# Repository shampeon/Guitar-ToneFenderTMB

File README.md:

A small PCB for the Fender AB763 treble, mid, and bass tone stack. Inspired by Tristan Collins's [Bandmaster PCB](https://github.com/tristancollins/Guitar-ToneBandmaster), with the same dimensions and for the PCB and mounting holes, and created in KiCad 9.

# Components and their values

* R1: 100k (tone slope resistor, 0.5W or greater)
* C1: 250pF (treble capacitor, 400V or greater)
* C2: 100nF/0.1uF (bass capacitor, 400V or greater)
* C3: 4.7nF/0.0047uF (mid capacitor, 400V or greater)
* J1, J2: 2 pin screw terminal, 5mm spacing
* RV1, RV2, RV3: 3 pin screw terminal, 5mm spacing

You can adjust the values of the components to change the behavior of the tone stack. Select the Fender Treble-Mid-Bass tonestack at [Yet Another Tonestack Calculator](https://tonestack.yuriturov.com) to compare the frequency response to the standard values here.

The mid pot in this project is wired as a potentiometer, as in the Bassman 5F6-A, not a variable resistor as in the AB763 black panel amps. This avoids the issue where the signal completely drops out when all the tone pots are turned down.

Rob Robinette has a great [page on how the TMB tone stack works](https://robrobinette.com/How_The_TMB_Tone_Stack_Works.htm).

# Fabricating the PCB

The 53mm x 45mm PCB can be manufactured by any of the online PCB fabrication sites, like [PCBWay](https://pcbway.com) or [JLCPCB](https://jlcpcb.com/). I use PCBWay, so the back text `WayWayWay` will be converted to the PCBWay product number when it is manufactured. You may want to modify this if you use another manufacturer.

A Gerber file ZIP is included in the repository, generated using the PCBWay plugin for KiCad 9.

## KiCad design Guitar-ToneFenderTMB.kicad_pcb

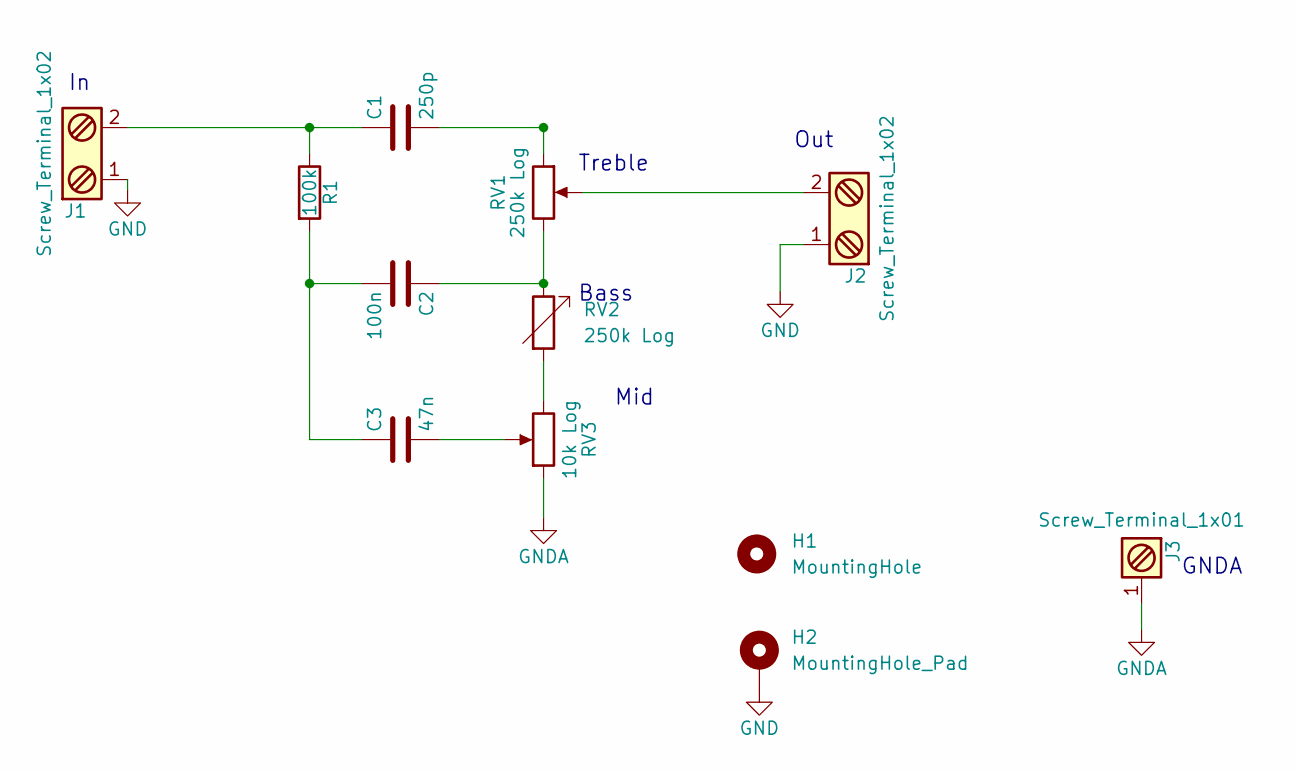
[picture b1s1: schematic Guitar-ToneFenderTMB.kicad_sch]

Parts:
C1: 250p; C_Disc_D7.5mm_W5.0mm_P7.50mm
C2: 100n; C_Rect_L7.2mm_W4.5mm_P5.00mm_FKS2_FKP2_MKS2_MKP2
C3: 47n; C_Axial_L12.0mm_D6.5mm_P15.00mm_Horizontal
H1: MountingHole; MountingHole_3.2mm_M3
H2: MountingHole_Pad; MountingHole_3.2mm_M3_Pad
J1, J2: Screw_Terminal_1x02; PhoenixContact_MCV_1,5_2-G-5.08_1x02_P5.08mm_Vertical
J3: Screw_Terminal_1x01; SolderWire-0.75sqmm_1x01_D1.25mm_OD2.3mm
R1: 100k; R_Axial_DIN0414_L11.9mm_D4.5mm_P15.24mm_Horizontal
RV1: 250k Log; PhoenixContact_MCV_1,5_3-G-5.08_1x03_P5.08mm_Vertical; MPN 1729131
RV2: 250k Log; PhoenixContact_MCV_1,5_3-G-5.08_1x03_P5.08mm_Vertical
RV3: 10k Log; PhoenixContact_MCV_1,5_3-G-5.08_1x03_P5.08mm_Vertical; MPN 1729131

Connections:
GND: H2.1, J1.1, J2.1
GNDA: J3.1, RV3.1
unnamed: C1.1, J1.2, R1.1
unnamed: C1.2, RV1.1
unnamed: C2.1, RV1.3, RV2.1
unnamed: C2.2, C3.1, R1.2
unnamed: C3.2, RV3.2
unnamed: J2.2, RV1.2
unnamed: RV2.2, RV3.3

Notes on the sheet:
Treble
Out
Bass
Mid
GNDA

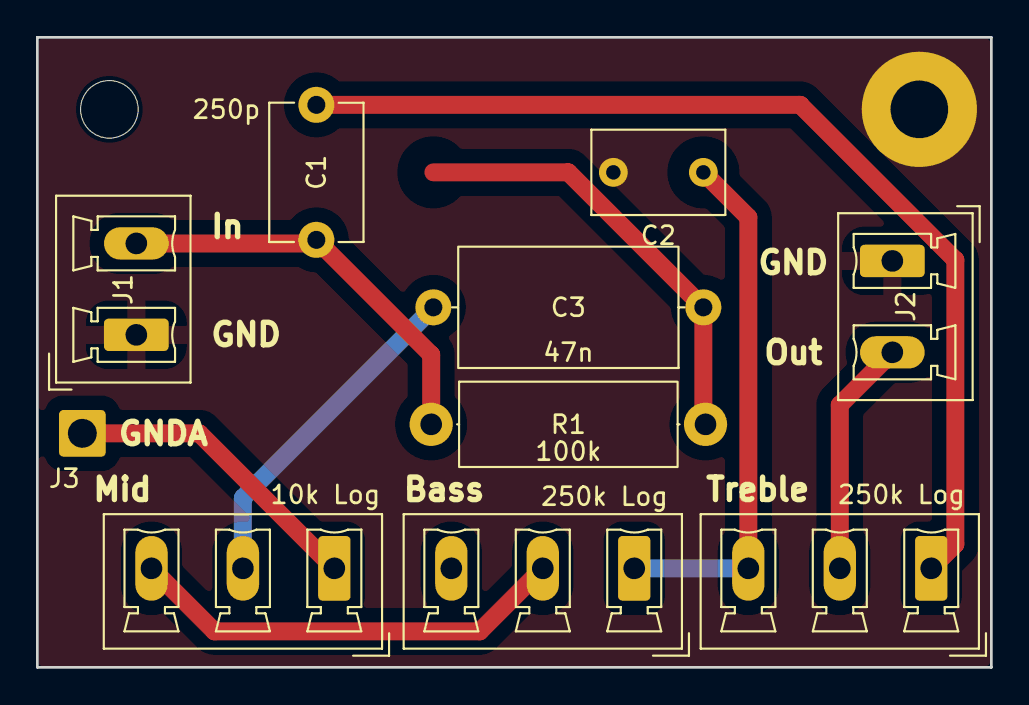
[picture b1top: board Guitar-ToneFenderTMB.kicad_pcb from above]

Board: 2 copper layers, 53.0 x 35.0 mm, 12 parts (0 on the bottom side), 9 nets.

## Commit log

2025-08-15 Initialize repo.
2025-08-26 Fixed C3 value to 47n
